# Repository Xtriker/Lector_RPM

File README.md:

# Lector_RPM
Lector de RPM mediante STM32L412 y displays de 7 segmentos

Este proyecto es realizado mediante el software STM32CubeIDE y puede ser portadeado hacia cualquier tarjeta compatible con este software.
Este medidor puede desplegar valores desde 0 RPM y mayor de 9999.

El funcionamiento es el siguiente:

1. Mediante un transductor del tipo infrarrojo con su respectivo phototransistor, el LED infrarrojo tendrá una resistencia de 82 Ohms para evitar el daño del LED; el phototransistor esta en modo pull-up mediante una resistencia de 1kohm.

2. Este transductor se coloca en el PIN PC10 de la STM32L412, estas entradas pueden ser cambiadas a cualquier pin de la tarjeta, ya que se realizó macros con el nombre "Detener"; si se realiza cambio del pin, colocar el nombre como se encuentra la macro.

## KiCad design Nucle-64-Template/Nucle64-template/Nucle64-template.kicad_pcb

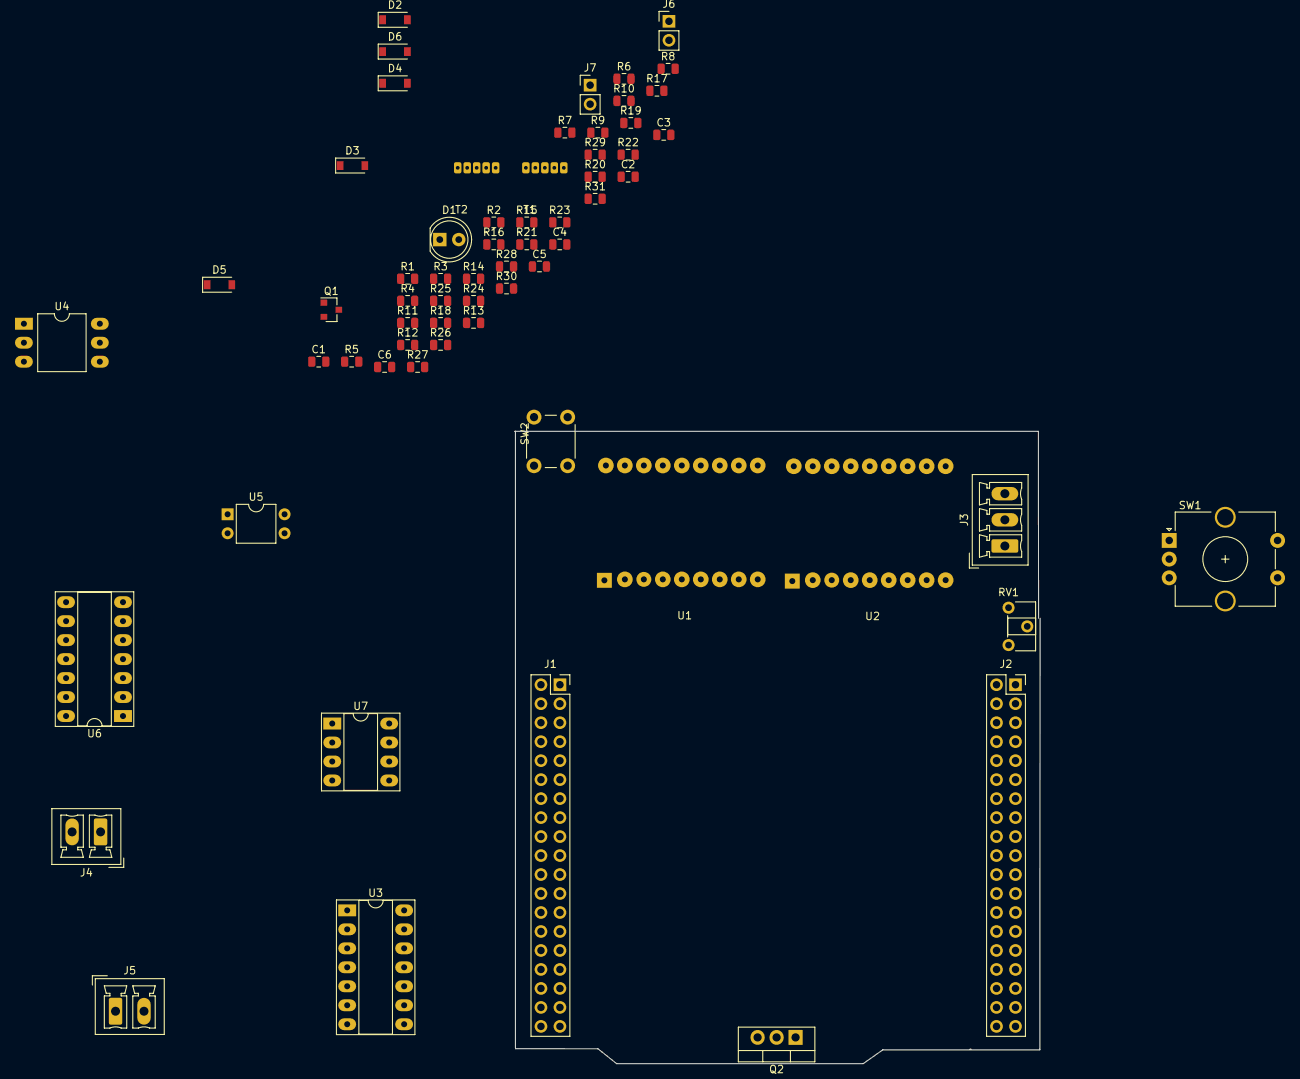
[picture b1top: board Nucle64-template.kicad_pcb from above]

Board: 2 copper layers, 70.3 x 84.6 mm, 64 parts (0 on the bottom side), 64 nets, no tracks yet.

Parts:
C1, C2, C3, C4: 0.1µF; C_0805_2012Metric
C5: 100nF; C_0805_2012Metric
C6: 33nF; C_0805_2012Metric
D1: LED; LED_D5.0mm
D2, D3, D4, D5, D6: 1N4007; D_SOD-123
J1, J2: Conn_02x19_Top_Bottom; PinSocket_2x19_P2.54mm_Vertical
J3: Screw_Terminal_01x03; PhoenixContact_MCV_1,5_3-G-3.5_1x03_P3.50mm_Vertical
J4, J5: Screw_Terminal_01x02; PhoenixContact_MCV_1,5_2-G-3.81_1x02_P3.81mm_Vertical
J6, J7: Conn_01x02_Male; PinHeader_1x02_P2.54mm_Vertical
Q1: 2N2219; SOT-23
Q2: BTA16; TO-220-3_Vertical
R1, R2, R11, R12: 1K5; R_0805_2012Metric
R3, R4, R5, R6, R7, R8, R9, R10, R21, R22, R30: 100R; R_0805_2012Metric
R13, R14, R15, R16, R19, R20, R26, R27: 10k; R_0805_2012Metric
R17, R18, R31: 10K; R_0805_2012Metric
R23: 1K; R_0805_2012Metric
R24: 47; R_0805_2012Metric
R25: 180R; R_0805_2012Metric
R28: 2k2; R_0805_2012Metric
R29: 33R; R_0805_2012Metric
RV1: 50K; Potentiometer_ACP_CA6-H2,5_Horizontal
SW1: Rotary_Encoder_Switch; RotaryEncoder_Alps_EC12E-Switch_Vertical_H20mm_CircularMoun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
SW2: SW_Push; SW_PUSH_6mm
T1, T2: 2SA798
U1, U2: DUY14A2
U3, U6: 74HC14; DIP-14_W7.62mm_Socket_LongPads
U4: MOC3021M; DIP-6_W10.16mm_LongPads
U5: PC817; DIP-4_W7.62mm
U7: TL081; DIP-8_W7.62mm_Socket_LongPads

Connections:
+3V3: J3.1, R13.1, R14.2, R18.1, R20.1, R26.2, R30.1, T1.3, T2.3
+5V: J3.3, R31.1, RV1.1, U7.7
A: R10.2, U1.11, U1.16, U2.11, U2.16
B: R6.2, U1.10, U1.15, U2.10, U2.15
C: R9.2, U1.3, U1.8, U2.3, U2.8
D: R5.2, U1.2, U1.6, U2.2, U2.6
DP: R3.2, U1.4, U1.9, U2.4, U2.9
E: R8.2, U1.1, U1.5, U2.1, U2.5
F: R4.2, U1.12, U1.18, U2.12, U2.18
G: R7.2, U1.7, U1.17, U2.7, U2.17
GND: C1.1, C2.1, C3.1, C4.2, D1.1, D2.2, J1.10, J1.23, J1.29, J1.30, J2.5, J2.29, J3.2, J6.2, J7.2, Q1.1, R24.2, RV1.3, SW1.C, SW1.S2, SW2.1, U5.3, U7.4
NC: J1.5, J1.6, J1.11, J1.24, J1.32
unnamed: C1.2, R13.2, R15.2, U3.5
unnamed: C2.2, R14.1, R16.2, U3.9
unnamed: C3.2, R17.1, R18.2, U3.3
unnamed: C4.1, R19.1, R20.2, U3.1
unnamed: C5.1, R25.1, R28.2
unnamed: C5.2, J5.2, Q2.1, R27.2, R29.2
unnamed: C6.1, J5.1, Q2.2, R28.1
unnamed: C6.2, R29.1
unnamed: D1.2, R21.2
unnamed: D2.1, Q1.3, R22.1, U4.1
unnamed: D3.1, D6.2, J4.2
unnamed: D3.2, D4.2, U5.2
unnamed: D4.1, D5.2, J4.1
unnamed: D5.1, D6.1, R23.2
unnamed: J6.1, R30.2
unnamed: J7.1, R31.2, U7.2
unnamed: Q1.2, R24.1, U4.2
unnamed: Q2.3, R27.1, U4.4
unnamed: R1.1, T1.1
unnamed: R2.1, T1.5
unnamed: R11.1, T2.1
unnamed: R12.1, T2.5
unnamed: R15.1, SW1.A
unnamed: R16.1, SW1.B
unnamed: R17.2, SW1.S1
unnamed: R19.2, SW2.2
unnamed: R23.1, U5.1
unnamed: R25.2, U4.6
unnamed: R26.1, U5.4, U6.11
unnamed: RV1.2, U7.3
unnamed: T1.2, U1.14
unnamed: T1.4, U1.13
unnamed: T2.2, U2.14
unnamed: T2.4, U2.13
unnamed: U6.13, U7.6
PA0: J1.33, R5.1
PA8: J2.10, R10.1
PA12: J2.17, R1.2
PA15: J2.14, R2.2
PB5: J2.15, R11.2
PB6: J2.11, U3.4
PB8: J2.2, U3.6
PB10: J2.13, R12.2
PC1: J1.37, R6.1
PC2: J1.36, R9.1
PC4: J2.36, R8.1
PC6: J2.21, R4.1
PC7: J2.12, R7.1
PC8: J2.20, R3.1
PC9: J2.1, U6.10
PC10: J1.1, U3.2
PC11: J1.20, R21.1, R22.2

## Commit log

2020-06-07 Se añade proyecto y documentación
2020-06-08 Se globaliza librería a STM32F1
    La librería de 7 Segmentos ahora es posible usarla en STM32F103 y STM32L412
2020-06-08 Implementación de función para desplegar letras en display
2020-06-08 Realizacion del ejemplo para la impresion
    Contador de 0 a 999
2020-06-12 Se realiza una maquina de estados
    Se implementa una maquina de estados para la mejor visualización de las revoluciones en el display
2020-06-13 Implementacion debounce y lectura Hz
2020-06-14 Correcto funcionamiento y prueba del medidor de RPM
    Se realiza la prueba física del medidor de RPM, se desplegan correctamente los datos en el display de 7 segmentos.
2020-06-14 Pin in/out usados
2020-06-14 Imagen configuracion Timer
2020-06-14 Se coloca diagrama de conexiones
2020-06-14 Correción del esquemático
2020-06-14 Corrección en los voltajes del traductor
2020-06-14 Imágenes de la implementación.
2020-06-14 Unificación a una sola librería
2020-06-22 Implementación de controlador PID
    Implementacion de controlador PID en la maquina de estados
2020-06-22 Implementación de interrupcion en PC13
2020-06-24 Implementación del encoder mecanico
    Se coloca un encoder mecánico para cambiar los valores de 0 a 9; en un futuro se usará para cambiar los valores de la RPM en el display de 7 segmentos.
2020-06-24 Implementacion del cambio de valor con el Encoder
    Mediante el encoder e interupciones del sistemas es posible cambiar los valores de lo que sera las variaciones de las RPM del control PID.
2020-06-25 Se colocar libreria PID de github
2020-06-30 Modificación libreria despliegue
    Ahora es posible el uso de ambos tipos de display de 7 segmentos (anodo y catodo) ademas de la implementacion de un 5 displays.
2020-07-01 Correccion de datos flotantes y lectura
    Se realiza correcion de lectura en el display catodo comun de 7 segmentos, ahora se tienen 5 segmentos y un mayor rango de lectura
2020-07-01 Correccion de desbordamiento de datos
    Se corrige error de desbordamiento en la libreria despliegue.h
2020-07-01 Se establece los limites de las RPM
    Se establece los limites de RPM a 35,000 , para evitar daños en hardware
2020-07-03 Prueba experimental del dimmer y el cruce por cero
2020-07-04 Prueba del dimmer digital
2020-07-05 Modificación del tiempo de encendido del SCR y el despliegue
    Se realiza una modificación en la función Espera(); ahora colocando un argumento llamado Tiempo en milisegundos, este parametro es escencial para la activacion del SCR, ademas de implementar el despl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
2020-07-07 Correcto funcionamiento del dimmer
2020-07-08 Creacion de la libreria de app_SpindleController.h
    Se realizar el controlador PID para un router de 1/4 HP
2020-07-08 Cambio de valores Ki, Kp y Kd
2020-07-09 Cambio del tiempo del dimmer
2020-07-09 Solucion de problemas de impresion de digitos en el dimmer
    Se soluciona el pulsado de la carga AC y la impresion de los datos en el display de 7 segmentos
2020-07-10 Se realiza libreria app_DigitalDimmer.h
    Se realiza libreria para la realizacion de pruebas, se logro un optimo funcionamiento
2020-07-13 Cambio de la función de lectura de frecuencia
    Se realiza una nueva forma de realizar la lectura de la frecuencia del spindle, esta nueva forma es mediante interrupciones del timer; minimizando el tiempo de ejecución entre cada una de las tareas.
2020-07-14 Modificación de los Timer, y cambio Debounce
    Se realiza modificación de Tiempo de los TImer, y se realiza una modificación a la función app_Debounce();, la lectura de cada uno de los timers es de 1 ms en el timer1 y de 1us en el timer 2
2020-07-15 Primer prueba fisica del controlador PID
    Es necesario realizar un promedio de las lecturas y cambiar los valores del controlador PID
2020-07-15 Se realiza un promedio de la lectura de la frecuencia
2020-07-15 2da prueba del controlador PID
    En esta segunda prueba el controlador se comporto mas responsivo en la lectura de las RPM, es necesario modificador los valores Ki, Dp y Kd
2020-07-18 NUCLEO-L412RB-P Shield
2020-07-19 Creación del digrama esquemático
2020-07-19 Reconfiguracion del timer
2020-07-19 Se importa documentación del proyecto
2020-07-21 Modificacion del debounce.c y debounce.h
2020-07-22 Creación del porteo del controlador PID a STM32F103
2020-07-22 Nueva librerias
    Creación de la librería app_Delay.h, app_Debounce.h y app_MAX7212.h
2020-07-22 Se realizan cambios del porteo de Encoder.h
2020-07-23 Se realiza modificación de la libreria app_MAX7912.h
2020-07-24 Implementación de la librería app_MAX7912
    Se realiza prueba física del Encoder y MAX7912
2020-07-24 Cambio de Encoder por Push Botton
2020-07-24 Implementacion del controlador PID al STM32F103
2020-07-26 Implementación del controlador PID en STM32F103
2020-07-28 Solucion del menu de seleccion el app_Dimmer(uint16_t Frecuencia)
2020-07-28 Modificación del tiempo de activación del SSR
2020-08-10 Modificación de adquisición de frecuencia
